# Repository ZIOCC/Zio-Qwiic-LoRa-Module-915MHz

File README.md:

# Zio Qwiic LoRa Module 915MHz
We referred sparkfun's gateway firmware, check SparkFun QwiicRF Library master [here](https://github.com/sparkfun/SparkFun_QwiicRF_Library)

> This module is available for purchase [here](https://www.smart-prototyping.com/Zio-Qwiic-Lora-Module-915MHz).

###### Description

This is a US compatible LoRa module (SX1276, 915MHz). LoRa module can send and receive data in a very long distance but consume very low power. We made a Qwiic version of this LoRa module, no soldering and jumper wire connections, just Qwiic cable plugin, and have fun! 

LoRa module is powerful, it can send and receive data packets at up to 10KM distance, and consumes very low power (10mA for receiver, 120mA for transmitter).

LoRa itself is a SPI device, in order to turn it into a I2C device, we added a MCU (ATMEGA328P) as the gateway to do the dirty work for you, you just need to use the module’s I2C interface to communicate with the others. It is just that easy.
 
The button on the board is for pairing function, check [here](https://github.com/sparkfun/SparkFun_QwiicRF_Library/wiki) for more details.

> Note: This LoRa module is based on SX1276 RFM95W-915S2, the frequency is 915 MHz, check [here](https://www.thethingsnetwork.org/docs/lorawan/frequencies-by-country.html) to see if this can be used in your country.

###### Specification

* Voltage: 3.3V
* Interface: I2C
* LoRa IC: SX1276 RFM95W-915S2
* Distance: Up to 10KM
* Gateway MCU: ATMEGA328P
* Dimension: 26.0 x 41.6 mm
* Weight: 5.3g

###### Links

* [PCB Source file](https://github.com/ZIOCC/Zio-Qwiic-LoRa-Module-915MHz/tree/master/EAGLE)
* [PCB schematic](https://github.com/ZIOCC/Zio-Qwiic-LoRa-Module-915MHz/blob/master/Zio%20Qwiic%20LoRa%20module%20915mhz.pdf)
* [Demo Code](https://github.com/ZIOCC/Zio-Qwiic-LoRa-Module-915MHz/tree/master/Demo%20Code/Qwiic_RF_I2C_Pairing)
* [Gateway firmware](https://github.com/sparkfun/SparkFun_QwiicRF_Library)

###### About Zio
> Zio is a new line of open sourced, compact, and grid layout boards, fully integrated for Arduino and Qwiic ecosystem. Designed ideally for wearables, robotics, small-space limitations or other on the go projects. Check out other awesome Zio products [here](https://www.smart-prototyping.com/Zio).

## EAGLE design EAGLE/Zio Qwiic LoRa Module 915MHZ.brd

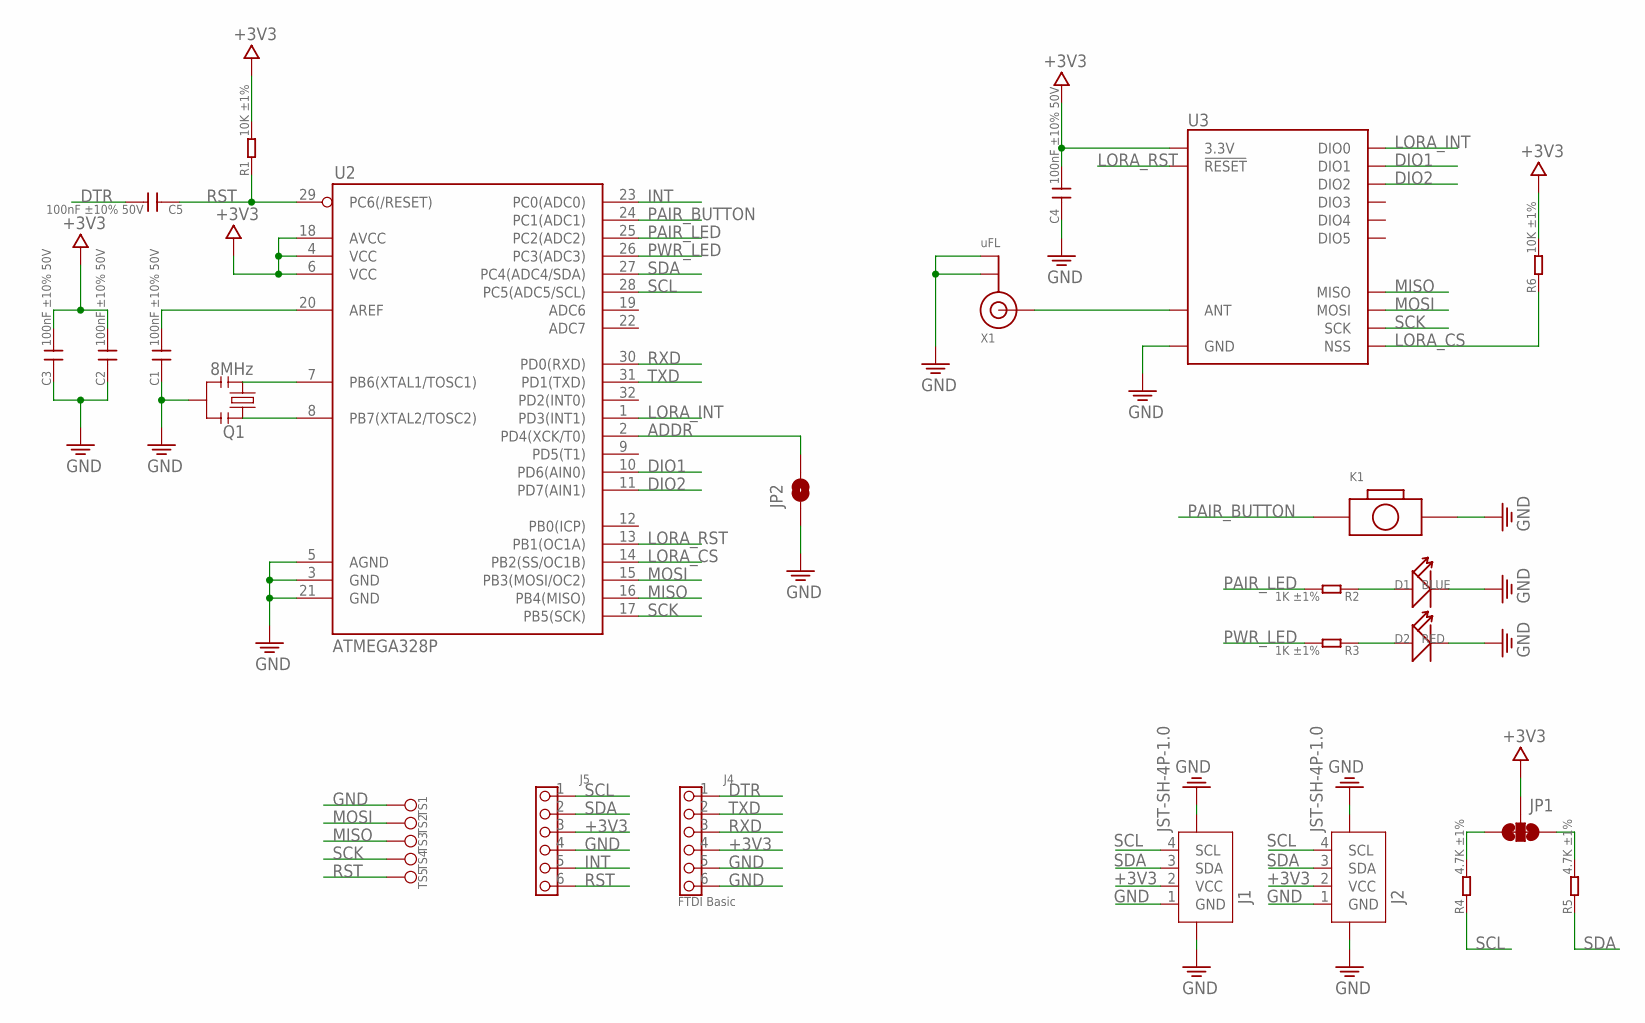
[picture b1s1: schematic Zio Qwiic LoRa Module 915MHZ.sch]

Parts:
C1, C2, C3, C4, C5: 100nF ±10% 50V; C0603
D1: BLUE; LED-0603
D2: RED; LED-0603
J1, J2: JST-SH-4P-1.0; JST-SH-4P
J4: FTDI Basic; 6P-2.54-60/35MIL
J5: HEADER-6P-60/35MIL; 6P-2.54-60/35MIL
JP1: SMT-JUMPER_3_2-NC_TRACE
JP2: JUMPER-SMT_2_NC_PASTE_NOCREM; SMT-JUMPER_2_NC_PASTE_SILK_NOCREM
K1: BOTTON-2PSKRKAEE020; SKRKAEE020
Q1: 8MHz; RESONATOR-SMD
R1, R6: 10K ±1%; R0603
R2, R3: 1K ±1%; R0603
R4, R5: 4.7K ±1%; R0603
TS1, TS2, TS3, TS4, TS5: TEST_POINT35MIL; 1P-35MIL
U2: ATMEGA328P; TQFP32-08
U3: SPARKX_RFM96W; SPARKX_RFM95/96/97/98W
X1: uFL; U.FL

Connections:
+3V3: C2.2, C3.2, C4.2, J1.2 (VCC), J2.2 (VCC), J4.4, J5.3, JP1.2, R1.2, R6.2, U2.4 (VCC), U2.6 (VCC), U2.18 (AVCC), U3.3.3V
ADDR: JP2.2, U2.2 (PD4(XCK/T0))
DIO1: U2.10 (PD6(AIN0)), U3.DIO1
DIO2: U2.11 (PD7(AIN1)), U3.DIO2
DTR: C5.2, J4.1
GND: C1.1, C2.1, C3.1, C4.1, D1.-, D2.-, J1.1 (GND), J1.NC1 (5), J1.NC2 (6), J2.1 (GND), J2.NC1 (5), J2.NC2 (6), J4.5, J4.6, J5.4, JP2.1, K1.2, Q1.2, TS1.P$1, U2.3 (GND), U2.5 (AGND), U2.21 (GND), U3.GND@1 (GND), U3.GND@2 (GND), U3.GND@3 (GND), X1.1 (GND), X1.2 (GND)
INT: J5.5, U2.23 (PC0(ADC0))
LORA_CS: R6.1, U2.14 (PB2(SS/OC1B)), U3.NSS
LORA_INT: U2.1 (PD3(INT1)), U3.DIO0
LORA_RST: U2.13 (PB1(OC1A)), U3.!RESET
MISO: TS3.P$1, U2.16 (PB4(MISO)), U3.MISO
MOSI: TS2.P$1, U2.15 (PB3(MOSI/OC2)), U3.MOSI
unnamed: D1.+, R2.1
unnamed: D2.+, R3.1
unnamed: Q1.3, U2.7 (PB6(XTAL1/TOSC1))
unnamed: Q1.1, U2.8 (PB7(XTAL2/TOSC2))
unnamed: C1.2, U2.20 (AREF)
unnamed: U3.ANT, X1.3 (SIGNAL)
unnamed: JP1.3, R4.2
unnamed: JP1.1, R5.2
PAIR_BUTTON: K1.1, U2.24 (PC1(ADC1))
PAIR_LED: R2.2, U2.25 (PC2(ADC2))
PWR_LED: R3.2, U2.26 (PC3(ADC3))
RST: C5.1, J5.6, R1.1, TS5.P$1, U2.29 (PC6(/RESET))
RXD: J4.3, U2.30 (PD0(RXD))
SCK: TS4.P$1, U2.17 (PB5(SCK)), U3.SCK
SCL: J1.4 (SCL), J2.4 (SCL), J5.1, R4.1, U2.28 (PC5(ADC5/SCL))
SDA: J1.3 (SDA), J2.3 (SDA), J5.2, R5.1, U2.27 (PC4(ADC4/SDA))
TXD: J4.2, U2.31 (PD1(TXD))

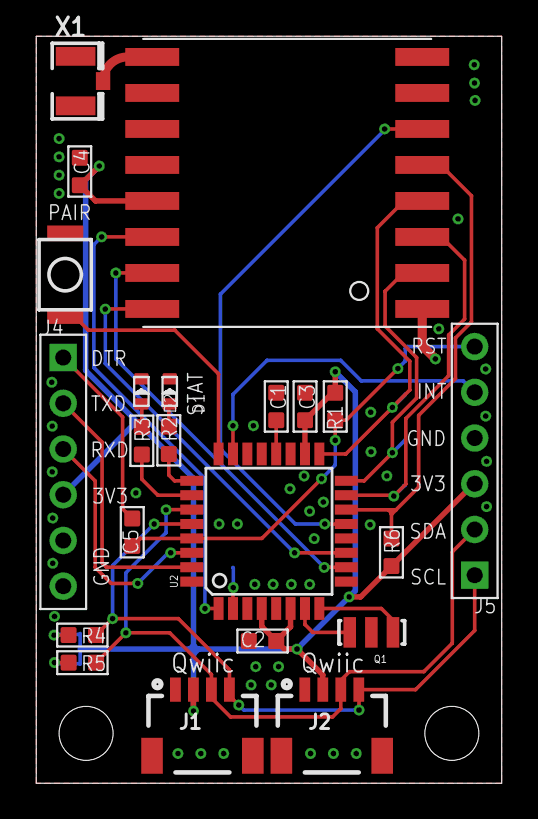
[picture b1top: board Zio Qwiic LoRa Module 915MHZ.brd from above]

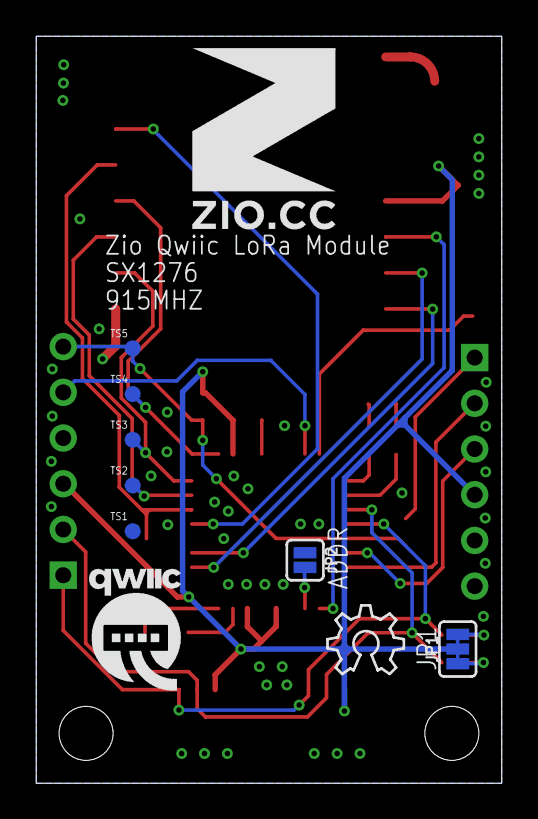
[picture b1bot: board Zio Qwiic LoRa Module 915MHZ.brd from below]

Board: 2 copper layers, 25.9 x 41.5 mm, 32 parts (10 on the bottom side), 29 nets.

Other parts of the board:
U$10: 10MM
U$11: QWIIC-LOGO-MEDIUM
U$12: OSHW_6X150_NOTEXT

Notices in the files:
parts and their libraries:
microbuilder: This work is placed in the public domain, and may be freely used for commercial and non-commercial work with the following conditions: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
